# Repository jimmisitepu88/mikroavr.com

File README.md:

# mikroavr.com

1. Seven Segment Project

I have some project how to drive seven segment with size 3", this my first project with large seven segment. I use IC 74HC595 as shift register and IC ULN2803 to power up at seven segment 3". I think sure, 5volt will not bright seven segment. 

for testing system, I use atmel Studio 7 and ATmega32. Atmel studio is awesome compiler for ATMEL microprocessor. for more detail i write ini https://mikroavr.com/rangkaian-seven-segment/

2. Digital Clock with DS3231

we have tiny project how to make digital clock with Arduino using RTC DS3231 and display to LCD16x2 with interface I2C. So this project will you see two I2C interface, one for DS3231 and other for I2C LCD, for more detail, you can se on my personal website https://mikroavr.com/jam-digital-arduino-ds3231/

Thanks

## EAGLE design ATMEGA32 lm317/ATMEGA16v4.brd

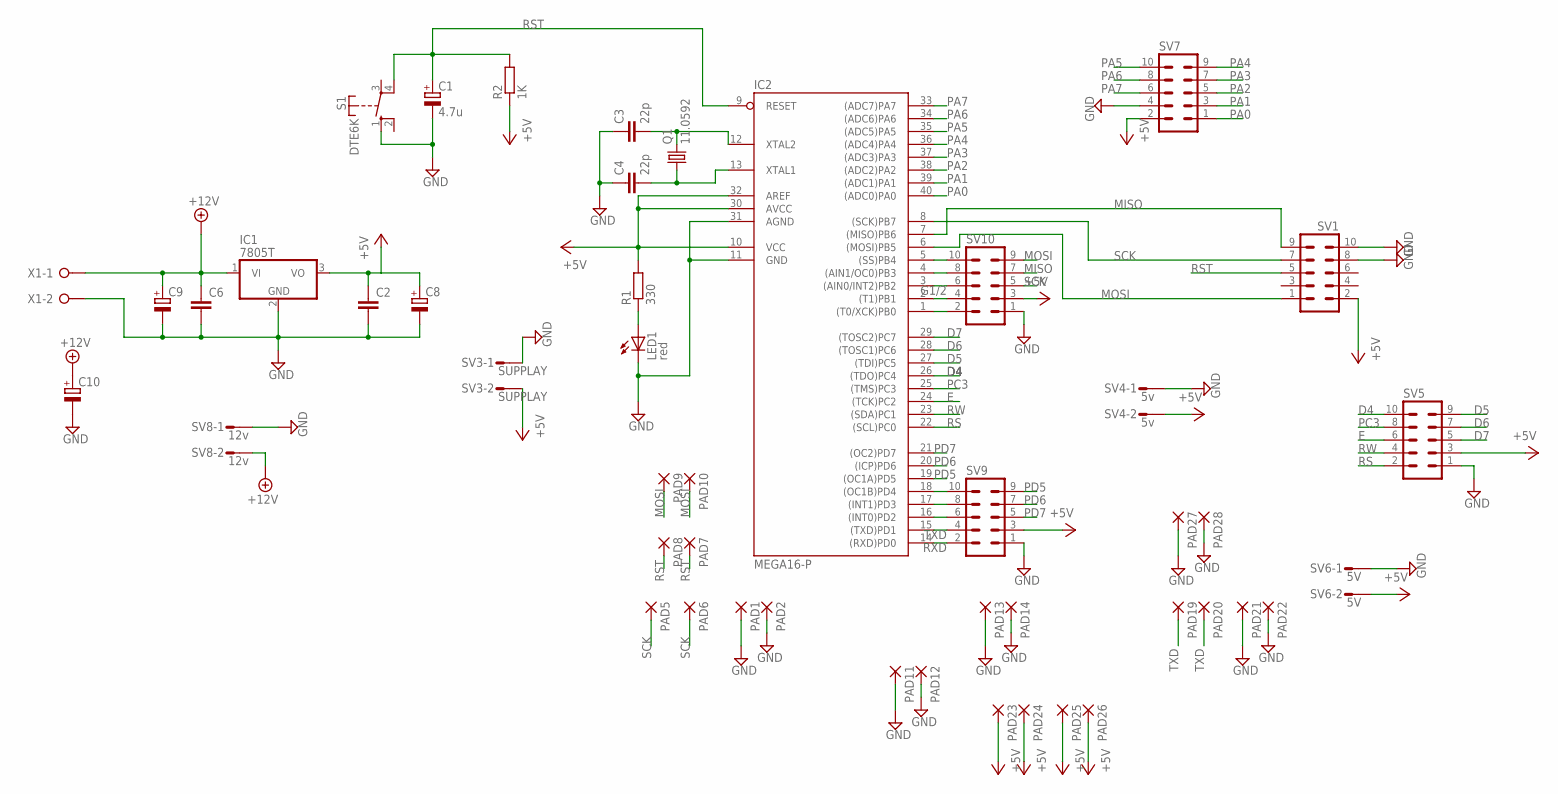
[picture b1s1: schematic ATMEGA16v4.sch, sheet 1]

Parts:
C1: 4.7u; E2-5
C2, C6: C-EU050-050X075; C050-050X075
C3, C4: 22p; C025-040X050
C8, C9: CPOL-EUE2.5-7; E2,5-7
C10: CPOL-EUE5-13; E5-13
IC1: 7805T; TO220H
IC2: MEGA16-P; DIL40
LED1: red; LED3MM
PAD1, PAD2, PAD5, PAD6, PAD7, PAD8, PAD9, PAD10, PAD11, PAD12, PAD13, PAD14, PAD19, PAD20, PAD21, PAD22, PAD23, PAD24, PAD25, PAD26, PAD27, PAD28: 1,6/0,9
Q1: 11.0592; HC49U-V
R1: 330; 0309/12
R2: 1K; 0309/12
S1: DTE6K
SV1, SV5, SV7, SV9, SV10: ML10
SV3: SUPPLAY; L02P
SV4: 5v; L02P
SV6: 5V; L02P
SV8: 12v; L02P
X1: W237-02P; W237-132

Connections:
+5V: C2.1, C8.+, IC1.3 (VO), IC2.10 (VCC), IC2.30 (AVCC), IC2.32 (AREF), PAD23.1, PAD24.1, PAD25.1, PAD26.1, R1.2, R2.1, SV1.2, SV3.2, SV4.2, SV5.3, SV6.2, SV7.2, SV9.3, SV10.3
+12V: C6.1, C9.+, C10.+, IC1.1 (VI), SV8.2, X1.1; also elsewhere on the board
D4: IC2.26 ((TDO)PC4), SV5.10
D5: IC2.27 ((TDI)PC5), SV5.9
D6: IC2.28 ((TOSC1)PC6), SV5.7
D7: IC2.29 ((TOSC2)PC7), SV5.5
E: IC2.24 ((TCK)PC2), SV5.6
G1/2: IC2.2 ((T1)PB1), SV10.4
GND: C1.-, C2.2, C3.1, C4.1, C6.2, C8.-, C9.-, C10.-, IC1.2 (GND), IC2.11 (GND), IC2.31 (AGND), LED1.K (C), PAD1.1, PAD2.1, PAD11.1, PAD12.1, PAD13.1, PAD14.1, PAD21.1, PAD22.1, PAD27.1, PAD28.1, S1.1 (S), SV1.8, SV1.10, SV3.1, SV4.1, SV5.1, SV6.1, SV7.4, SV8.1, SV9.1, SV10.1, X1.2; also elsewhere on the board
MISO: IC2.7 ((MISO)PB6), SV1.9, SV10.7
MOSI: IC2.6 ((MOSI)PB5), PAD9.1, PAD10.1, SV1.1, SV10.9
unnamed: LED1.A, R1.1
unnamed: C3.2, IC2.12 (XTAL2), Q1.2
unnamed: C4.2, IC2.13 (XTAL1), Q1.1
unnamed: IC2.18 ((OC1B)PD4), SV9.10
unnamed: IC2.17 ((INT1)PD3), SV9.8
unnamed: IC2.16 ((INT0)PD2), SV9.6
unnamed: IC2.5 ((SS)PB4), SV10.10
unnamed: IC2.4 ((AIN1/OC0)PB3), SV10.8
unnamed: IC2.3 ((AIN0/INT2)PB2), SV10.6
unnamed: IC2.1 ((T0/XCK)PB0), SV10.2
PA0: IC2.40 ((ADC0)PA0), SV7.1
PA1: IC2.39 ((ADC1)PA1), SV7.3
PA2: IC2.38 ((ADC2)PA2), SV7.5
PA3: IC2.37 ((ADC3)PA3), SV7.7
PA4: IC2.36 ((ADC4)PA4), SV7.9
PA5: IC2.35 ((ADC5)PA5), SV7.10
PA6: IC2.34 ((ADC6)PA6), SV7.8
PA7: IC2.33 ((ADC7)PA7), SV7.6
PC3: IC2.25 ((TMS)PC3), SV5.8
PD5: IC2.19 ((OC1A)PD5), SV9.9
PD6: IC2.20 ((ICP)PD6), SV9.7
PD7: IC2.21 ((OC2)PD7), SV9.5
RS: IC2.22 ((SCL)PC0), SV5.2
RST: C1.+, IC2.9 (RESET), PAD7.1, PAD8.1, R2.2, S1.4, SV1.5
RW: IC2.23 ((SDA)PC1), SV5.4
RXD: IC2.14 ((RXD)PD0), SV9.2; also elsewhere on the board
SCK: IC2.8 ((SCK)PB7), PAD5.1, PAD6.1, SV1.7, SV10.5
TXD: IC2.15 ((TXD)PD1), PAD19.1, PAD20.1, SV9.4; also elsewhere on the board

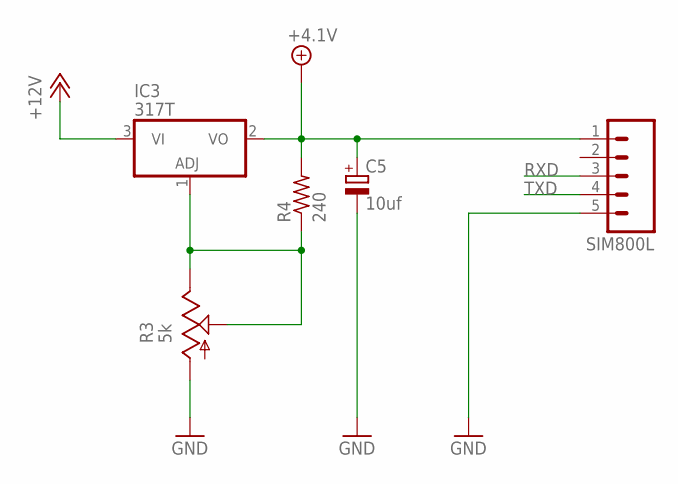
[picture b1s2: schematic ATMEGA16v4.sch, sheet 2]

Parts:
C5: 10uf; E2,5-5
IC3: 317T; TO220H
R3: 5k; CA6V
R4: 240; 0207/12
SIM800L: M05; 05P

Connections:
+4.1V: C5.+, IC3.2 (VO), R4.2, SIM800L.1
+12V: IC3.3 (VI); also elsewhere on the board
GND: C5.-, R3.A, SIM800L.5; also elsewhere on the board
unnamed: IC3.1 (ADJ), R3.E, R3.S, R4.1
RXD: SIM800L.3; also elsewhere on the board
TXD: SIM800L.4; also elsewhere on the board

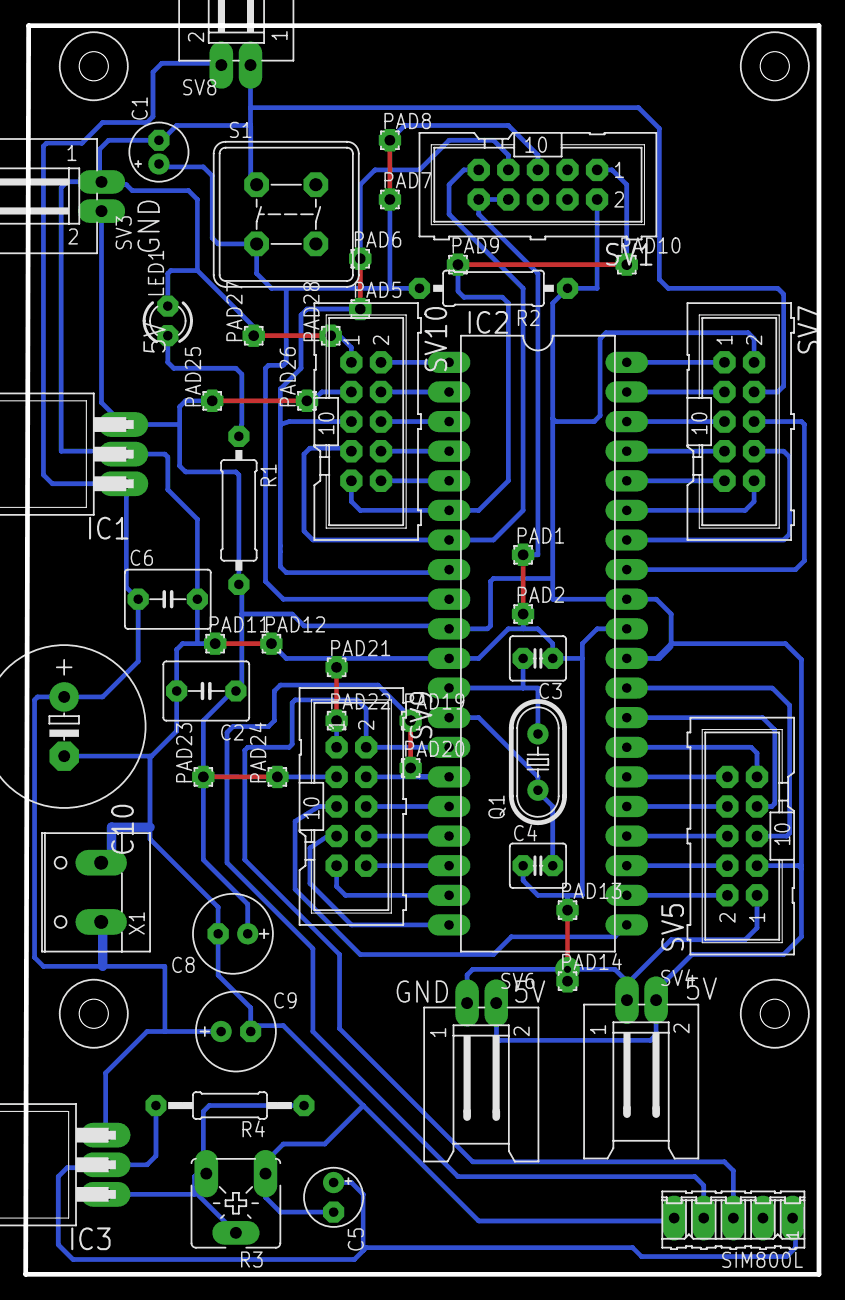
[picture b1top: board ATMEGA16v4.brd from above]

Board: 1 copper layer, 68.1 x 107.1 mm, 56 parts (0 on the bottom side), 41 nets.

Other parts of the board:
U$1, U$2, U$3, U$4: DRIL-2,5

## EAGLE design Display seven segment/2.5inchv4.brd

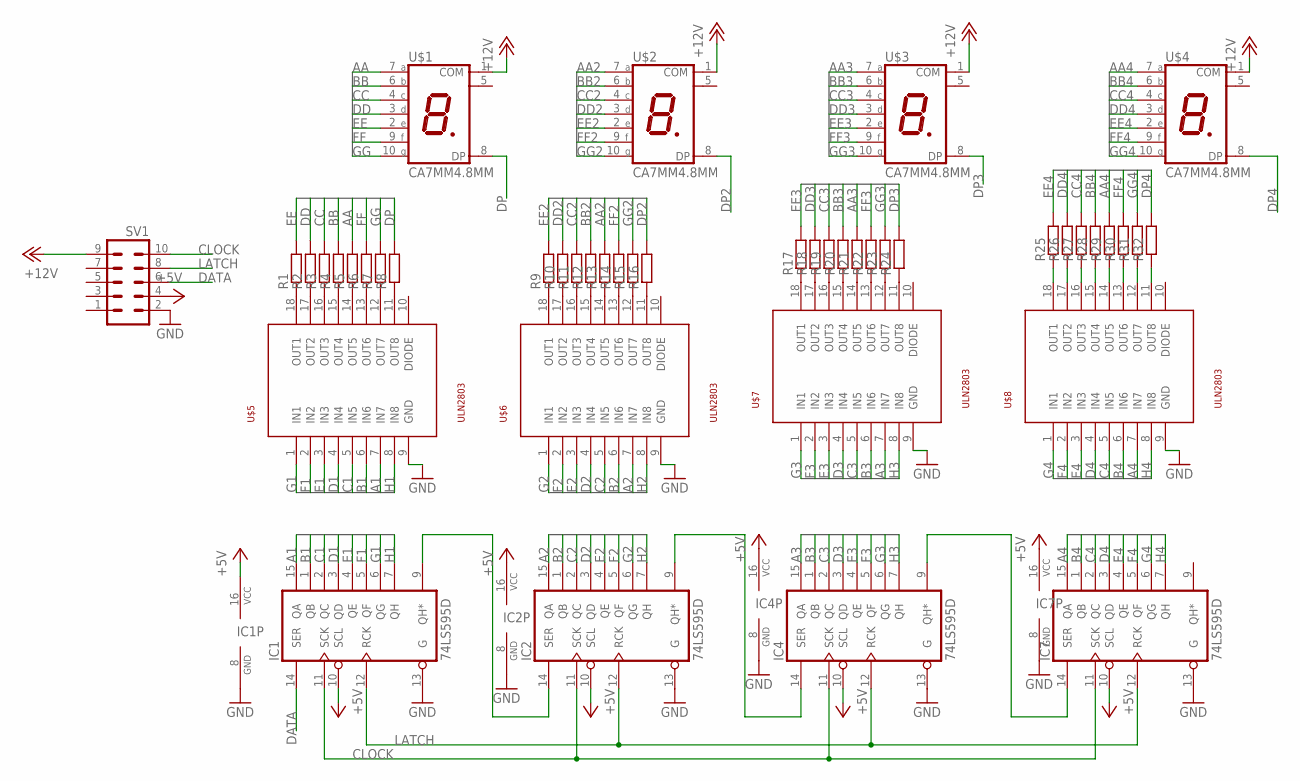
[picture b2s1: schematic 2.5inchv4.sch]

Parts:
IC1, IC2, IC4, IC7: 74LS595D; SO16
R1, R2, R3, R4, R5, R6, R7, R8, R9, R10, R11, R12, R13, R14, R15, R16, R17, R18, R19, R20, R21, R22, R23, R24, R25, R26, R27, R28, R29, R30, R31, R32: R-EU_0207/12; 0207/12
SV1: ML10
U$1, U$2, U$3, U$4: CA7MM4.8MM; CA7MM*4.8MM
U$5, U$6, U$7, U$8: ULN2803; SO18L

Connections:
+5V: IC1.10 (SCL), IC1.16 (VCC), IC2.10 (SCL), IC2.16 (VCC), IC4.10 (SCL), IC4.16 (VCC), IC7.10 (SCL), IC7.16 (VCC), SV1.4
+12V: SV1.9, U$1.1 (COM), U$2.1 (COM), U$3.1 (COM), U$4.1 (COM)
A1: IC1.15 (QA), U$5.7 (IN7)
A2: IC2.15 (QA), U$6.7 (IN7)
A3: IC4.15 (QA), U$7.7 (IN7)
A4: IC7.15 (QA), U$8.7 (IN7)
AA: R5.2, U$1.7 (A)
AA2: R13.2, U$2.7 (A)
AA3: R21.2, U$3.7 (A)
AA4: R29.2, U$4.7 (A)
B1: IC1.1 (QB), U$5.6 (IN6)
B2: IC2.1 (QB), U$6.6 (IN6)
B3: IC4.1 (QB), U$7.6 (IN6)
B4: IC7.1 (QB), U$8.6 (IN6)
BB: R4.2, U$1.6 (B)
BB2: R12.2, U$2.6 (B)
BB3: R20.2, U$3.6 (B)
BB4: R28.2, U$4.6 (B)
C1: IC1.2 (QC), U$5.5 (IN5)
C2: IC2.2 (QC), U$6.5 (IN5)
C3: IC4.2 (QC), U$7.5 (IN5)
C4: IC7.2 (QC), U$8.5 (IN5)
CC: R3.2, U$1.4 (C)
CC2: R11.2, U$2.4 (C)
CC3: R19.2, U$3.4 (C)
CC4: R27.2, U$4.4 (C)
CLOCK: IC1.11 (SCK), IC2.11 (SCK), IC4.11 (SCK), IC7.11 (SCK), SV1.10
D1: IC1.3 (QD), U$5.4 (IN4)
D2: IC2.3 (QD), U$6.4 (IN4)
D3: IC4.3 (QD), U$7.4 (IN4)
D4: IC7.3 (QD), U$8.4 (IN4)
DATA: IC1.14 (SER), SV1.6
DD: R2.2, U$1.3 (D)
DD2: R10.2, U$2.3 (D)
DD3: R18.2, U$3.3 (D)
DD4: R26.2, U$4.3 (D)
DP: R8.2, U$1.8 (DP)
DP2: R16.2, U$2.8 (DP)
DP3: R24.2, U$3.8 (DP)
DP4: R32.2, U$4.8 (DP)
E1: IC1.4 (QE), U$5.3 (IN3)
E2: IC2.4 (QE), U$6.3 (IN3)
E3: IC4.4 (QE), U$7.3 (IN3)
E4: IC7.4 (QE), U$8.3 (IN3)
EE: R1.2, U$1.2 (E)
EE2: R9.2, U$2.2 (E)
EE3: R17.2, U$3.2 (E)
EE4: R25.2, U$4.2 (E)
F1: IC1.5 (QF), U$5.2 (IN2)
F2: IC2.5 (QF), U$6.2 (IN2)
F3: IC4.5 (QF), U$7.2 (IN2)
F4: IC7.5 (QF), U$8.2 (IN2)
FF: R6.2, U$1.9 (F)
FF2: R14.2, U$2.9 (F)
FF3: R22.2, U$3.9 (F)
FF4: R30.2, U$4.9 (F)
G1: IC1.6 (QG), U$5.1 (IN1)
G2: IC2.6 (QG), U$6.1 (IN1)
G3: IC4.6 (QG), U$7.1 (IN1)
G4: IC7.6 (QG), U$8.1 (IN1)
GG: R7.2, U$1.10 (G)
GG2: R15.2, U$2.10 (G)
GG3: R23.2, U$3.10 (G)
GG4: R31.2, U$4.10 (G)
GND: IC1.8 (GND), IC1.13 (G), IC2.8 (GND), IC2.13 (G), IC4.8 (GND), IC4.13 (G), IC7.8 (GND), IC7.13 (G), SV1.2, U$5.9 (GND), U$6.9 (GND), U$7.9 (GND), U$8.9 (GND)
H1: IC1.7 (QH), U$5.8 (IN8)
H2: IC2.7 (QH), U$6.8 (IN8)
H3: IC4.7 (QH), U$7.8 (IN8)
H4: IC7.7 (QH), U$8.8 (IN8)
LATCH: IC1.12 (RCK), IC2.12 (RCK), IC4.12 (RCK), IC7.12 (RCK), SV1.8
unnamed: IC1.9 (QH*), IC2.14 (SER)
unnamed: IC2.9 (QH*), IC4.14 (SER)
unnamed: IC4.9 (QH*), IC7.14 (SER)
unnamed: R1.1, U$5.18 (OUT1)
unnamed: R2.1, U$5.17 (OUT2)
unnamed: R3.1, U$5.16 (OUT3)
unnamed: R4.1, U$5.15 (OUT4)
unnamed: R5.1, U$5.14 (OUT5)
unnamed: R6.1, U$5.13 (OUT6)
unnamed: R7.1, U$5.12 (OUT7)
unnamed: R8.1, U$5.11 (OUT8)
unnamed: R9.1, U$6.18 (OUT1)
unnamed: R10.1, U$6.17 (OUT2)
unnamed: R11.1, U$6.16 (OUT3)
unnamed: R12.1, U$6.15 (OUT4)
unnamed: R13.1, U$6.14 (OUT5)
unnamed: R14.1, U$6.13 (OUT6)
unnamed: R15.1, U$6.12 (OUT7)
unnamed: R16.1, U$6.11 (OUT8)
unnamed: R17.1, U$7.18 (OUT1)
unnamed: R18.1, U$7.17 (OUT2)
unnamed: R19.1, U$7.16 (OUT3)
unnamed: R20.1, U$7.15 (OUT4)
unnamed: R21.1, U$7.14 (OUT5)
unnamed: R22.1, U$7.13 (OUT6)
unnamed: R23.1, U$7.12 (OUT7)
unnamed: R24.1, U$7.11 (OUT8)
unnamed: R25.1, U$8.18 (OUT1)
unnamed: R26.1, U$8.17 (OUT2)
unnamed: R27.1, U$8.16 (OUT3)
unnamed: R28.1, U$8.15 (OUT4)
unnamed: R29.1, U$8.14 (OUT5)
unnamed: R30.1, U$8.13 (OUT6)
unnamed: R31.1, U$8.12 (OUT7)
unnamed: R32.1, U$8.11 (OUT8)

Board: 1 copper layer, 45 parts (0 on the bottom side), 105 nets, no tracks yet.

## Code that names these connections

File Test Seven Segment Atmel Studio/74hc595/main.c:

/*
 * 74hc595.c
 *
 * Created: 9/13/2017 11:32:26 PM
 * Author : Jimmi Sitepu
 */ 

#define F_CPU 16000000UL
#include <avr/io.h>
#include <util/delay.h>

#define DATA PORTD4
#define CLOCK PORTD0
#define LATCH PORTD1

#define LATCH_0 PORTD = PORTD & ~(1<<PD1)
#define LATCH_1 PORTD = PORTD | (1<<PD1)

#define CLOCK_0 PORTD = PORTD & ~(1<<PD0)
#define CLOCK_1 PORTD = PORTD | (1<<PD0)

#define DATA_0 PORTD = PORTD & ~(1<<PD4)
#define DATA_1 PORTD = PORTD | (1<<PD4)


void displaySegment(uint8_t POS1);
void shiftOut(uint8_t val);

int main(void)
{
    /* Replace with your application code */
	
	DDRD = (1<<DDD5)|(1<<DDD4)|(1<<DDD1)|(1<<DDD0);//SET SEBAGAI OUTPUT
	PORTD = (0<<PORTD5)|(0<<PORTD4)|(0<<PORTD1)|(0<<PORTD0);
		
	
    while (1) 
    {
		displaySegment(0b01111111);
		_delay_ms(1000);
		displaySegment(0x00);
		_delay_ms(1000);
    }
}

void shiftOut(uint8_t val){
	uint8_t i;
	uint8_t data;
	for (i = 0; i < 8; i++)
	{
		data = val & (1<<(7-i));
		if (data == 0)
		{
			DATA_0;
		}
		else{
			DATA_1;
		}
		CLOCK_1;
		CLOCK_0;
		
	}
}

void displaySegment(uint8_t	POS1){
	
	LATCH_0;
	shiftOut(POS1);
	shiftOut(POS1);
	shiftOut(POS1);
	shiftOut(POS1);
	LATCH_1;
}

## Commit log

2017-11-17 lm317 atmega32 dengan sim800
    this circuit for lm317 atmega32 with sim800
2017-12-07 temp convertion with b4a, basic for android
    tutorial how to create app with b4a, basic for android, you can see detail with my web site https://mikroavr.com/tutorial-b4a-android-dasar/
2018-03-12 Add files via upload
    This my little project, how to make Digital clock with Arduino and RTC DS3231. Data digital clock will display in LCD 16x2 with I2C LCD, for more description you can see on my blog https://mikroavr.c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
2018-05-13 library seven segment
    add library seven segment for 4 digits
2018-05-13 add readme.md
    add description
